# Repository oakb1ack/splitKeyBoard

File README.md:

# Split keyboard

A 42-key split keyboard with a KiCad PCB and ZMK firmware for two XIAO
nRF52840 controllers. The left half connects to the host; the right half
connects to the left over Bluetooth.

- [PCB and schematics](src/pcb/README.md)
- [Firmware and keymap](src/firmware/README.md)

## License

Project files are available under the [MIT License](LICENSE). The included
parts from [marbastlib](src/pcb/marbastlib-main/LICENSE),
[Seeed OPL](src/pcb/OPL_Kicad_Library-master/LICENSE), and
[mouse-bite.pretty](src/pcb/mouse-bite.pretty/LICENSE) retain their own licenses.

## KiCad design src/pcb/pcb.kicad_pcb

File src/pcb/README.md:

# PCB

Open [pcb.kicad_pro](pcb.kicad_pro) in KiCad 10. The two halves are joined by
breakaway tabs in a panel about 244 × 103 mm.

The 42 switches use 19.05 mm pitch. The five main columns stagger by up to
3 mm between neighbors. The controllers and switch footprints are on the back.

## Schematic

The [root schematic](pcb.kicad_sch) contains left and right sheets. Preview the
[left](../../docs/schematic-left.svg) or [right](../../docs/schematic-right.svg)
half at full size.

Each half has its own XIAO controller, switch matrix, battery sensing circuit,
and local ground net. The halves communicate wirelessly after separation.

## Before ordering

The [Gerbers and drill files](Gerber-Files/) and [ZIP archive](Gerber-Files.zip)
were exported for this layout. The saved [DRC report](DRC.rpt) reports no
violations, unconnected pads, or schematic parity issues under the project's
enabled checks. It also lists checks that are disabled.

Physical keycap fit, case fit, and typing feel still need a prototype.

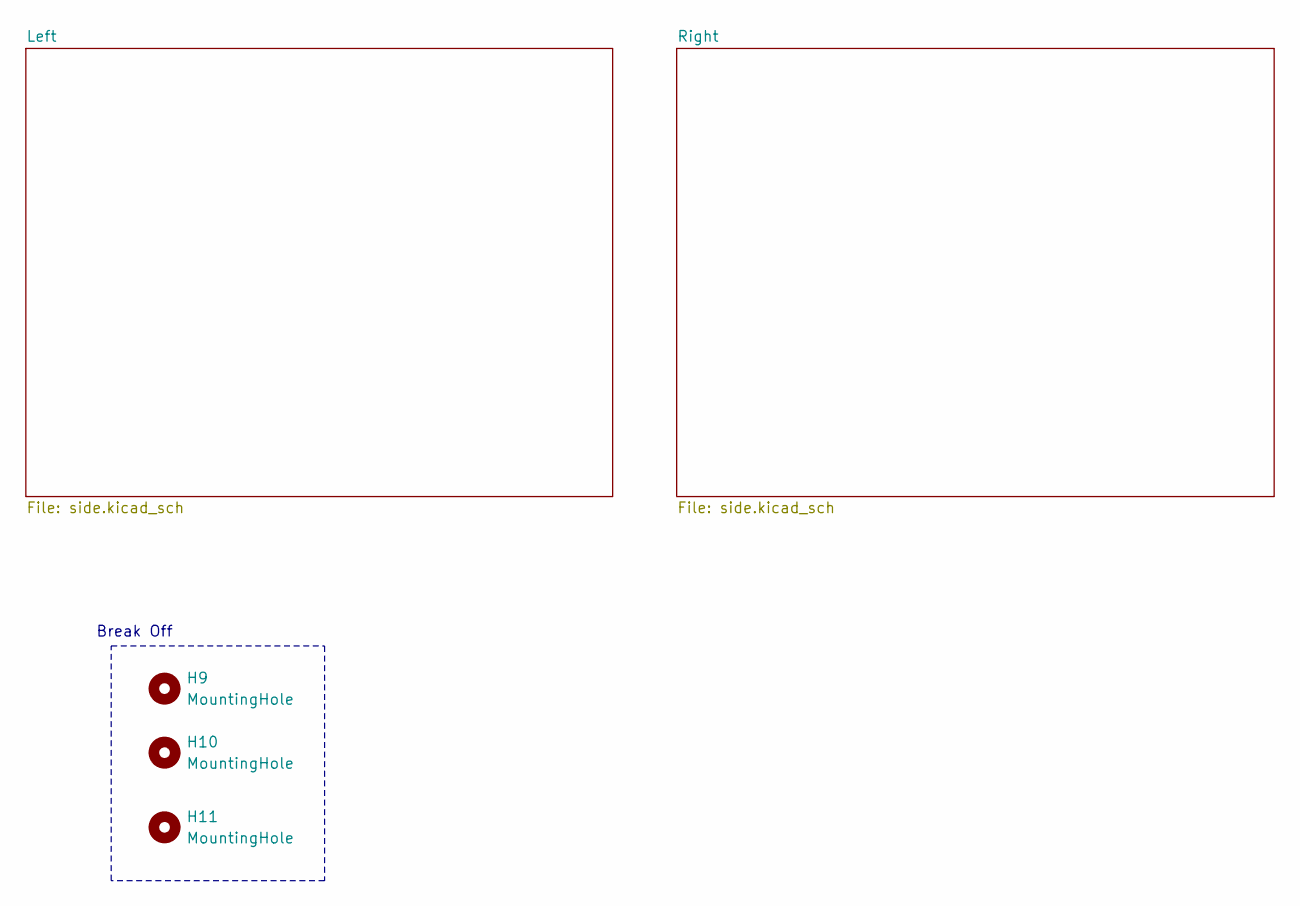
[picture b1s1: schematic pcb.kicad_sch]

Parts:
H9, H10, H11: MountingHole; mouse-bite-3mm-6mm

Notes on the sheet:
Break Off

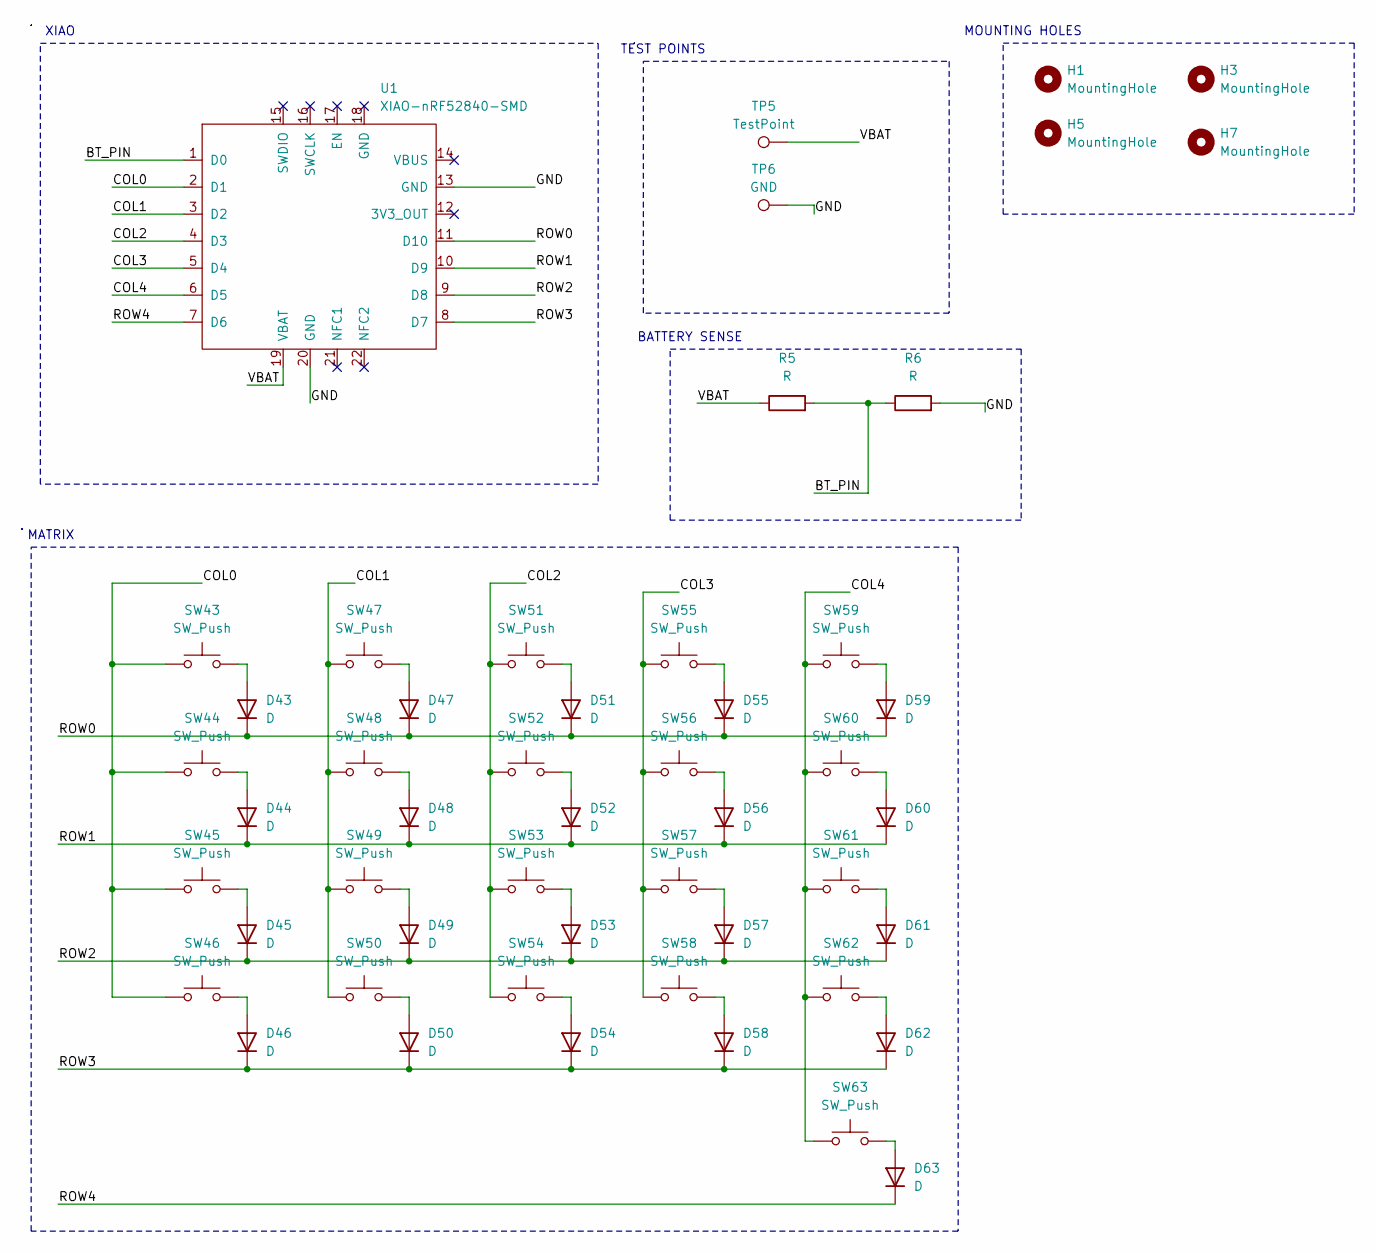
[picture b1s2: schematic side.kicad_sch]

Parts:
D43, D44, D45, D46, D47, D48, D49, D50, D51, D52, D53, D54, D55, D56, D57, D58, D59, D60, D61, D62, D63: D; D_SOD-123
H1, H3, H5, H7: MountingHole; MountingHole_2.2mm_M2
R5, R6: R; R_0805_2012Metric
SW43, SW44, SW45, SW46, SW47, SW48, SW49, SW50, SW51, SW52, SW53, SW54, SW55, SW56, SW57, SW58, SW59, SW60, SW61, SW62, SW63: SW_Push; SW_choc_v1_HS_CPG135001S30_1u
TP5: TestPoint; TestPoint_Pad_D2.0mm
TP6: GND; TestPoint_Pad_D2.0mm
U1: XIAO-nRF52840-SMD; modified-XIAO-nRF52840-SMD

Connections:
/Left/BT_PIN: R5.2, R6.1, U1.1 (D0)
/Left/COL0: SW43.1, SW44.1, SW45.1, SW46.1, U1.2 (D1)
/Left/COL1: SW47.1, SW48.1, SW49.1, SW50.1, U1.3 (D2)
/Left/COL2: SW51.1, SW52.1, SW53.1, SW54.1, U1.4 (D3)
/Left/COL3: SW55.1, SW56.1, SW57.1, SW58.1, U1.5 (D4)
/Left/COL4: SW59.1, SW60.1, SW61.1, SW62.1, SW63.1, U1.6 (D5)
/Left/GND: R6.2, TP6.1 (1_1), U1.13 (GND), U1.20 (GND)
/Left/ROW0: D43.1 (K), D47.1 (K), D51.1 (K), D55.1 (K), D59.1 (K), U1.11 (D10)
/Left/ROW1: D44.1 (K), D48.1 (K), D52.1 (K), D56.1 (K), D60.1 (K), U1.10 (D9)
/Left/ROW2: D45.1 (K), D49.1 (K), D53.1 (K), D57.1 (K), D61.1 (K), U1.9 (D8)
/Left/ROW3: D46.1 (K), D50.1 (K), D54.1 (K), D58.1 (K), D62.1 (K), U1.8 (D7)
/Left/ROW4: D63.1 (K), U1.7 (D6)
/Left/VBAT: R5.1, TP5.1 (1_1), U1.19 (VBAT)
unnamed: D43.2 (A), SW43.2
unnamed: D44.2 (A), SW44.2
unnamed: D45.2 (A), SW45.2
unnamed: D46.2 (A), SW46.2
unnamed: D47.2 (A), SW47.2
unnamed: D48.2 (A), SW48.2
unnamed: D49.2 (A), SW49.2
unnamed: D50.2 (A), SW50.2
unnamed: D51.2 (A), SW51.2
unnamed: D52.2 (A), SW52.2
unnamed: D53.2 (A), SW53.2
unnamed: D54.2 (A), SW54.2
unnamed: D55.2 (A), SW55.2
unnamed: D56.2 (A), SW56.2
unnamed: D57.2 (A), SW57.2
unnamed: D58.2 (A), SW58.2
unnamed: D59.2 (A), SW59.2
unnamed: D60.2 (A), SW60.2
unnamed: D61.2 (A), SW61.2
unnamed: D62.2 (A), SW62.2
unnamed: D63.2 (A), SW63.2

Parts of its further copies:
D64, D65, D66, D67, D68, D69, D70, D71, D72, D73, D74, D75, D76, D77, D78, D79, D80, D81, D82, D83, D84: D; D_SOD-123
H2, H4, H6, H8: MountingHole; MountingHole_2.2mm_M2
R7, R8: R; R_0805_2012Metric
SW64, SW65, SW66, SW67, SW68, SW69, SW70, SW71, SW72, SW73, SW74, SW75, SW76, SW77, SW78, SW79, SW80, SW81, SW82, SW83, SW84: SW_Push; SW_choc_v1_HS_CPG135001S30_1u
TP7: TestPoint; TestPoint_Pad_D2.0mm
TP8: GND; TestPoint_Pad_D2.0mm
U2: XIAO-nRF52840-SMD; modified-XIAO-nRF52840-SMD

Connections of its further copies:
/Right/BT_PIN: R7.2, R8.1, U2.1 (D0)
/Right/COL0: SW64.1, SW65.1, SW66.1, SW67.1, U2.2 (D1)
/Right/COL1: SW68.1, SW69.1, SW70.1, SW71.1, U2.3 (D2)
/Right/COL2: SW72.1, SW73.1, SW74.1, SW75.1, U2.4 (D3)
/Right/COL3: SW76.1, SW77.1, SW78.1, SW79.1, U2.5 (D4)
/Right/COL4: SW80.1, SW81.1, SW82.1, SW83.1, SW84.1, U2.6 (D5)
/Right/GND: R8.2, TP8.1 (1_1), U2.13 (GND), U2.20 (GND)
/Right/ROW0: D64.1 (K), D68.1 (K), D72.1 (K), D76.1 (K), D80.1 (K), U2.11 (D10)
/Right/ROW1: D65.1 (K), D69.1 (K), D73.1 (K), D77.1 (K), D81.1 (K), U2.10 (D9)
/Right/ROW2: D66.1 (K), D70.1 (K), D74.1 (K), D78.1 (K), D82.1 (K), U2.9 (D8)
/Right/ROW3: D67.1 (K), D71.1 (K), D75.1 (K), D79.1 (K), D83.1 (K), U2.8 (D7)
/Right/ROW4: D84.1 (K), U2.7 (D6)
/Right/VBAT: R7.1, TP7.1 (1_1), U2.19 (VBAT)
unnamed: D64.2 (A), SW64.2
unnamed: D65.2 (A), SW65.2
unnamed: D66.2 (A), SW66.2
unnamed: D67.2 (A), SW67.2
unnamed: D68.2 (A), SW68.2
unnamed: D69.2 (A), SW69.2
unnamed: D70.2 (A), SW70.2
unnamed: D71.2 (A), SW71.2
unnamed: D72.2 (A), SW72.2
unnamed: D73.2 (A), SW73.2
unnamed: D74.2 (A), SW74.2
unnamed: D75.2 (A), SW75.2
unnamed: D76.2 (A), SW76.2
unnamed: D77.2 (A), SW77.2
unnamed: D78.2 (A), SW78.2
unnamed: D79.2 (A), SW79.2
unnamed: D80.2 (A), SW80.2
unnamed: D81.2 (A), SW81.2
unnamed: D82.2 (A), SW82.2
unnamed: D83.2 (A), SW83.2
unnamed: D84.2 (A), SW84.2

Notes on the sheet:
MATRIX
TEST POINTS
BATTERY SENSE
MOUNTING HOLES
XIAO

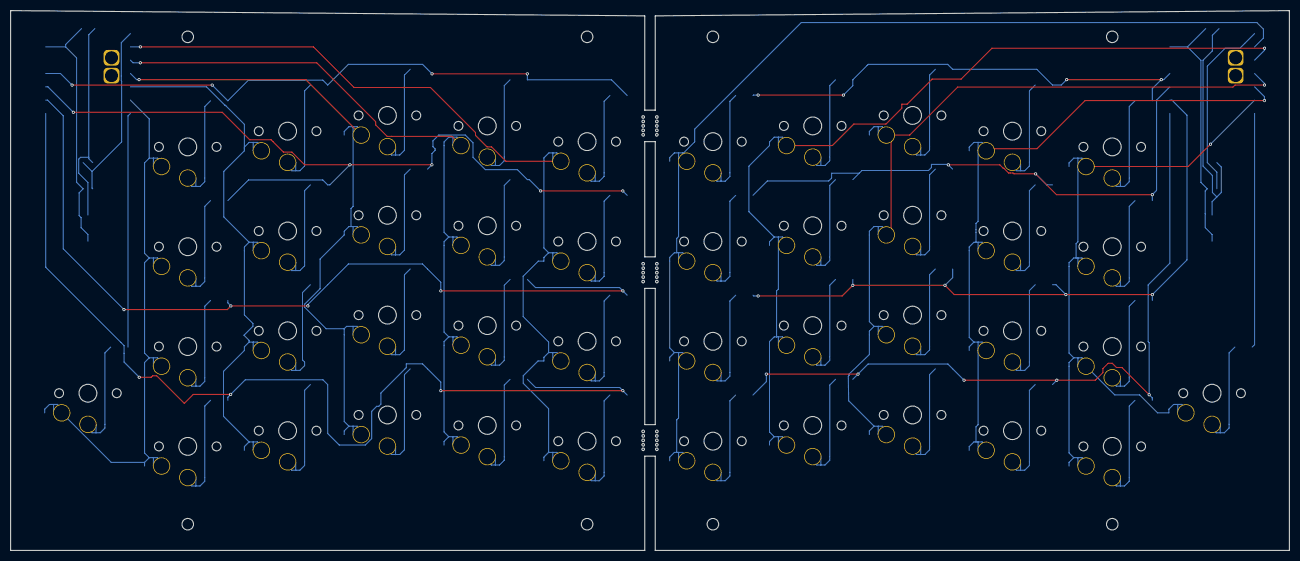
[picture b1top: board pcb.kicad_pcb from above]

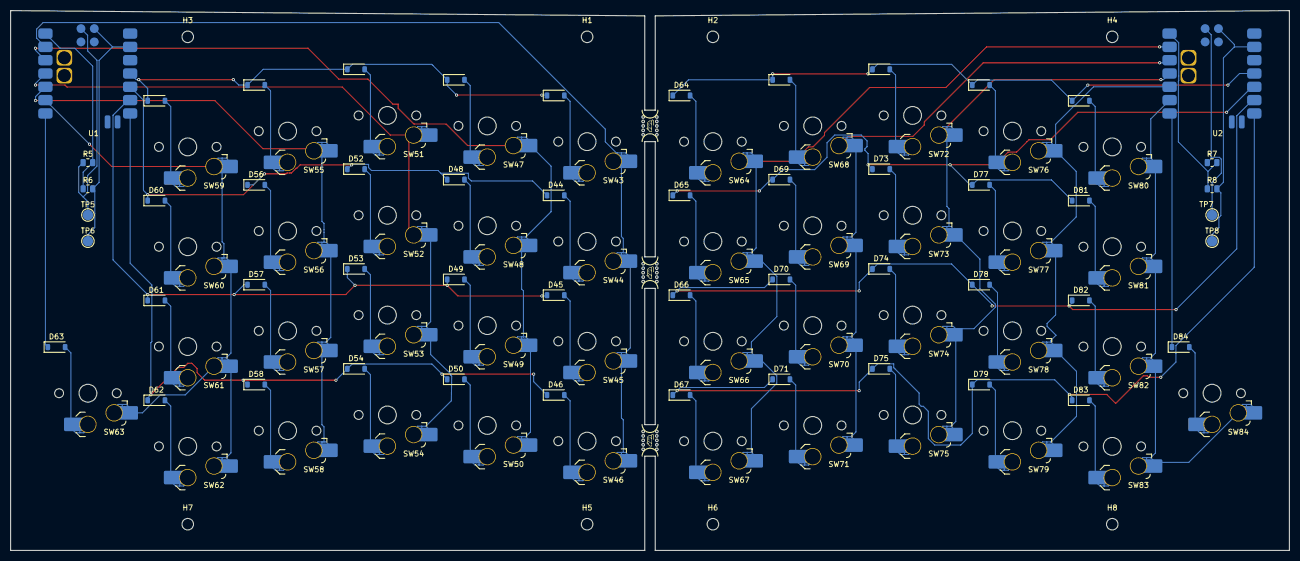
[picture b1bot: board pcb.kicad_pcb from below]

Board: 2 copper layers, 244.0 x 103.0 mm, 105 parts (105 on the bottom side), 68 nets.
